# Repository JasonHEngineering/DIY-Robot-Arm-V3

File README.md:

# DIY-Robot-Arm-V3 

Introduction - https://youtu.be/GQhKxkShxAY

# Parts Cost Estimation (SGD)

| Parts | Est. Cost (SGD) | Link |
|-------|----------------:|------|
| CNC parts (including shipping cost) | 740 | [CAD file in GitHub](https://github.com/JasonHEngineering/DIY-Robot-Arm-V3/tree/main/CAD%20(2d%20%2B%20step%20files)) |
| 3d printed parts (including shipping cost) | 69 | [CAD file in GitHub](https://github.com/JasonHEngineering/DIY-Robot-Arm-V3/tree/main/CAD%20(2d%20%2B%20step%20files)) |
| Main PCBA (5x, including SMD assembly & shipping cost) | 158 | [Design files in GitHub](https://github.com/JasonHEngineering/DIY-Robot-Arm-V3/tree/main/PCBA%20(schema%2C%20gerbers%2C%20kicad%20project)) |
| Encoder PCBA (10x, including SMD assembly & shipping cost) | 132 | [Design files in GitHub](https://github.com/JasonHEngineering/DIY-Robot-Arm-V3/tree/main/PCBA%20(schema%2C%20gerbers%2C%20kicad%20project)) |
| Bearing 6805 2RS (25x37x7mm) (3x) | 16.07 | [AliExpress](https://s.click.aliexpress.com/e/_c33xzexj) |
| Bearing lock nut M24x1.5x30x5 (3x) | 6.24 | [AliExpress](https://s.click.aliexpress.com/e/_c3OO3rFf) |
| M3 set screw with nylon head | 4.84 | [AliExpress](https://s.click.aliexpress.com/e/_c3lDO1O5) |
| Pulley (Bore 8mm, belt width 6 mm, 2GT-30T) | 4.48 | [AliExpress](https://s.click.aliexpress.com/e/_c4LLe4XL) |
| Pulley (Bore 12mm, belt width 6 mm, 2GT-30T) | 3.06 | [AliExpress](https://s.click.aliexpress.com/e/_c3QfG9gt) |
| Timing belt (2GT-200-6mm) | 1.02 | [AliExpress](https://s.click.aliexpress.com/e/_c4KhaszX) |
| Diametric Magnets for encoders (10 pcs / lot) | 3.68 | [AliExpress](https://s.click.aliexpress.com/e/_c3Axm1QN) |
| FFC cables (pitch 0.5 mm) | 6.00 | [AliExpress](https://s.click.aliexpress.com/e/_c4SXa38p) |
| Stepper motor cables (XH2.54) | 10.00 | [AliExpress](https://s.click.aliexpress.com/e/_c3dAdb65) |
| Stepper motor 60mm model 17CS07A-180 (2x) | 38.64 | [AliExpress](https://s.click.aliexpress.com/e/_c2yzH5rf) |
| Stepper motor 60mm model 17HS4023 (3x) | 25.29 | [AliExpress](https://s.click.aliexpress.com/e/_c4bld957) |
| Stepper motor 60mm model 17HS3401S-SZ (1x) | 12.29 | [AliExpress](https://s.click.aliexpress.com/e/_c31tJidB) |
| X17-30A harmonic reducer (30:1) (5x) | 338.00 | [AliExpress](https://s.click.aliexpress.com/e/_c3xNHvpT) |
| Raspberry Pi 4B, 4GB | 160.00 | [AliExpress](https://s.click.aliexpress.com/e/_c45i6ECJ) |
| ESP32-S3-DevKitC-1 (n16r8) | 14.63 | [AliExpress](https://s.click.aliexpress.com/e/_c41bdQlh) |
| Pins & connectors (22 pins) | 1.91 | [AliExpress](https://s.click.aliexpress.com/e/_c3fCAogH) |
| TMC2209 V1.3 motor drivers (6x) | 24.13 | [AliExpress](https://s.click.aliexpress.com/e/_c4b6KFWH) |
| 24V fan (60x60x15mm) | 2.89 | [AliExpress](https://s.click.aliexpress.com/e/_c3T1QZcp) |
| E-Stop Button | 4.15 | [AliExpress](https://s.click.aliexpress.com/e/_c3gcdvel) |
| DOIT ESP32 DEV KIT V1 | 7.27 | [AliExpress](https://s.click.aliexpress.com/e/_c3el80wp) |
| PS controller | 13.34 | [AliExpress](https://s.click.aliexpress.com/e/_c4OqUEGd) |
| Mini-560-Pro (Mini Pro 5V, 3A for Raspberry Pi) | 1.51 | [AliExpress](https://s.click.aliexpress.com/e/_c37WkxiV) |
| Optical Experiment Plate 5052 Aluminum 280x320x8mm | 71.25 | [AliExpress](https://s.click.aliexpress.com/e/_c3tvnmLj) |
| Servo Claw | 26.26 | [AliExpress](https://s.click.aliexpress.com/e/_c3I3E3Mh) |
| Servo motor MG996R | 6.74 | [AliExpress](https://s.click.aliexpress.com/e/_c3sTutbP) |
| Standoffs, clamps, dowel pins | 10.00 | |
| Fasteners | 10.00 | |

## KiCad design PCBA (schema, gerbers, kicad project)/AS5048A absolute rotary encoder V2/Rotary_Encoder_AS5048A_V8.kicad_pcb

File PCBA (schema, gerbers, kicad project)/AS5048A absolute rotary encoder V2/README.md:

# Notes 

1) Although there are 7 jumper pads here for purpose of using these encoders in series with SPI protocol, however due to GPIO0 on ESP32-S3 being a bootstrap pin, I will not be using jumper JP5 on the absolute encoder board at all. Consequently, the remaining chip select jumper for all the 6 axis encoders are allocated as shown in the table, with the soldering done accordingly.

<!-- wp:image {"id":4006,"sizeSlug":"large","linkDestination":"none"} -->
<figure class="wp-block-image size-large"></figure>
<!-- /wp:image -->

<!-- wp:image {"id":4002,"sizeSlug":"large","linkDestination":"none"} -->
<figure class="wp-block-image size-large"></figure>
<!-- /wp:image -->

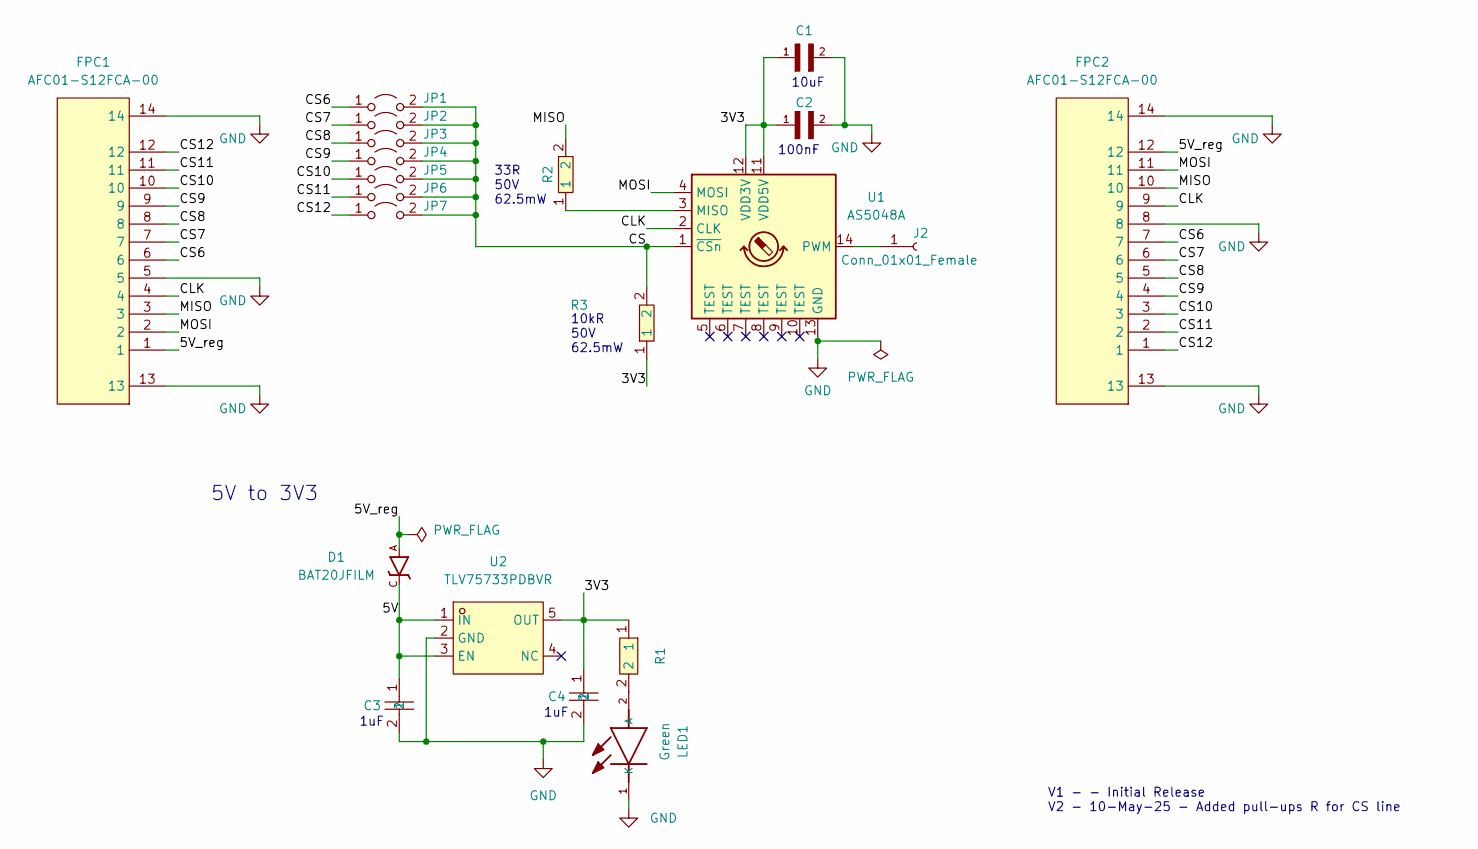
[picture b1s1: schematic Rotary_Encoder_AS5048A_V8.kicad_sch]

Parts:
C1: GRM155R60J106ME15D; CAPC1005X65N; LCSC C412251
C2: GCM155R71C104KA55J; CAPC1005X55N; LCSC C2655418
C3, C4: CC0603KRX7R7BB105; MLCC_16V_1uF_X7R_±10%_0603_C106248; LCSC Part C106248
D1: BAT20JFILM; SOD-323; LCSC Part # C155590
FPC1, FPC2: AFC01-S12FCA-00; FFC_conn_Flip type_12P_P=0.5mm_C262661; LCSC Part C262661
J2: Conn_01x01_Female; PinHeader_1x01_P1.00mm_Vertical
JP1, JP2, JP3, JP4, JP5, JP6, JP7: Jumper_2_Open; SolderJumper-2_P1.3mm_Open_TrianglePad1.0x1.5mm
LED1: Green; LEDC1608X80N; MOUSER_PART_NUMBER 710-150060GS75000
R1: 0402WGD1001TCE; Resistor_62.5mW_50V_±0.5%_1kΩ_0402_C407754; LCSC Part C407754
R2: RC0402FR-0733RL; Resistor_62.5mW_50V_±1%_33Ω_0402_C138002; LCSC Part C138002
R3: RC0402FR-0710KL; Resistor_62.5mW_50V_±1%_10kΩ_0402_C60490; LCSC Part C60490
U1: AS5048A; TSSOP-14_4.4x5mm_P0.65mm; LCSC C2655181
U2: TLV75733PDBVR; LDO_1A_Fixed_3.3V_out_5.5V_in_SOT-23-5_C485517; LCSC Part C485517

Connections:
/3V3: C1.1, C2.1, C4.1, R1.1, R3.1, U1.11 (VDD5V), U1.12 (VDD3V), U2.5 (OUT)
/5V: C3.1, D1.C, U2.1 (IN), U2.3 (EN)
/5V_reg: D1.A, FPC1.1, FPC2.12
/CLK: FPC1.4, FPC2.9, U1.2 (CLK)
/CS: JP1.2 (B), JP2.2 (B), JP3.2 (B), JP4.2 (B), JP5.2 (B), JP6.2 (B), JP7.2 (B), R3.2, U1.1 (~CSn)
/CS1: FPC1.6, FPC2.7, JP1.1 (A)
/CS2: FPC1.7, FPC2.6, JP2.1 (A)
/CS3: FPC1.8, FPC2.5, JP3.1 (A)
/CS4: FPC1.9, FPC2.4, JP4.1 (A)
/CS5: FPC1.10, FPC2.3, JP5.1 (A)
/CS6: FPC1.11, FPC2.2, JP6.1 (A)
/CS7: FPC1.12, FPC2.1, JP7.1 (A)
/MISO: FPC1.3, FPC2.10, R2.2
/MOSI: FPC1.2, FPC2.11, U1.4 (MOSI)
GND: C1.2, C2.2, C3.2, C4.2, FPC1.5, FPC1.13, FPC1.14, FPC2.8, FPC2.13, FPC2.14, LED1.1 (K), U1.13 (GND), U2.2 (GND)
unnamed: J2.1, U1.14 (PWM)
unnamed: LED1.2 (A), R1.2
unnamed: R2.1, U1.3 (MISO)

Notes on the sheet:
100nF
10kR 50V 62.5mW
1uF
33R 50V 62.5mW
5V to 3V3
10uF
V1 - - Initial Release V2 - 10-May-25 - Added pull-ups R for CS line

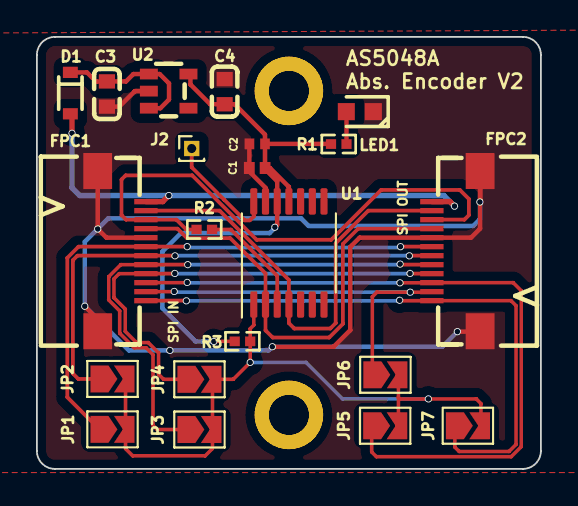
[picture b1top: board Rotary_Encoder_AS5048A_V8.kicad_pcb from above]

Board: 2 copper layers, 28.0 x 24.0 mm, 21 parts (0 on the bottom side), 18 nets.

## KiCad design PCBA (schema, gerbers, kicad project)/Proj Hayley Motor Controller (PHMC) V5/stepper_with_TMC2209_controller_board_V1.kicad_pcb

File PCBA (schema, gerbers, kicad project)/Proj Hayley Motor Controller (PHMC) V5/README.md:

# Notes 

1) Proven working in Arduino IDE 2.3.7
2) Servo is indeed GPIO 38 (J6 - pin 3), instead of the initial intent of GPIO 43 (J13 - pin 3), because the serial com line is always busy
3) JTAG must be disabled - because all the pins are used for the purpose of motor driving or some functions already

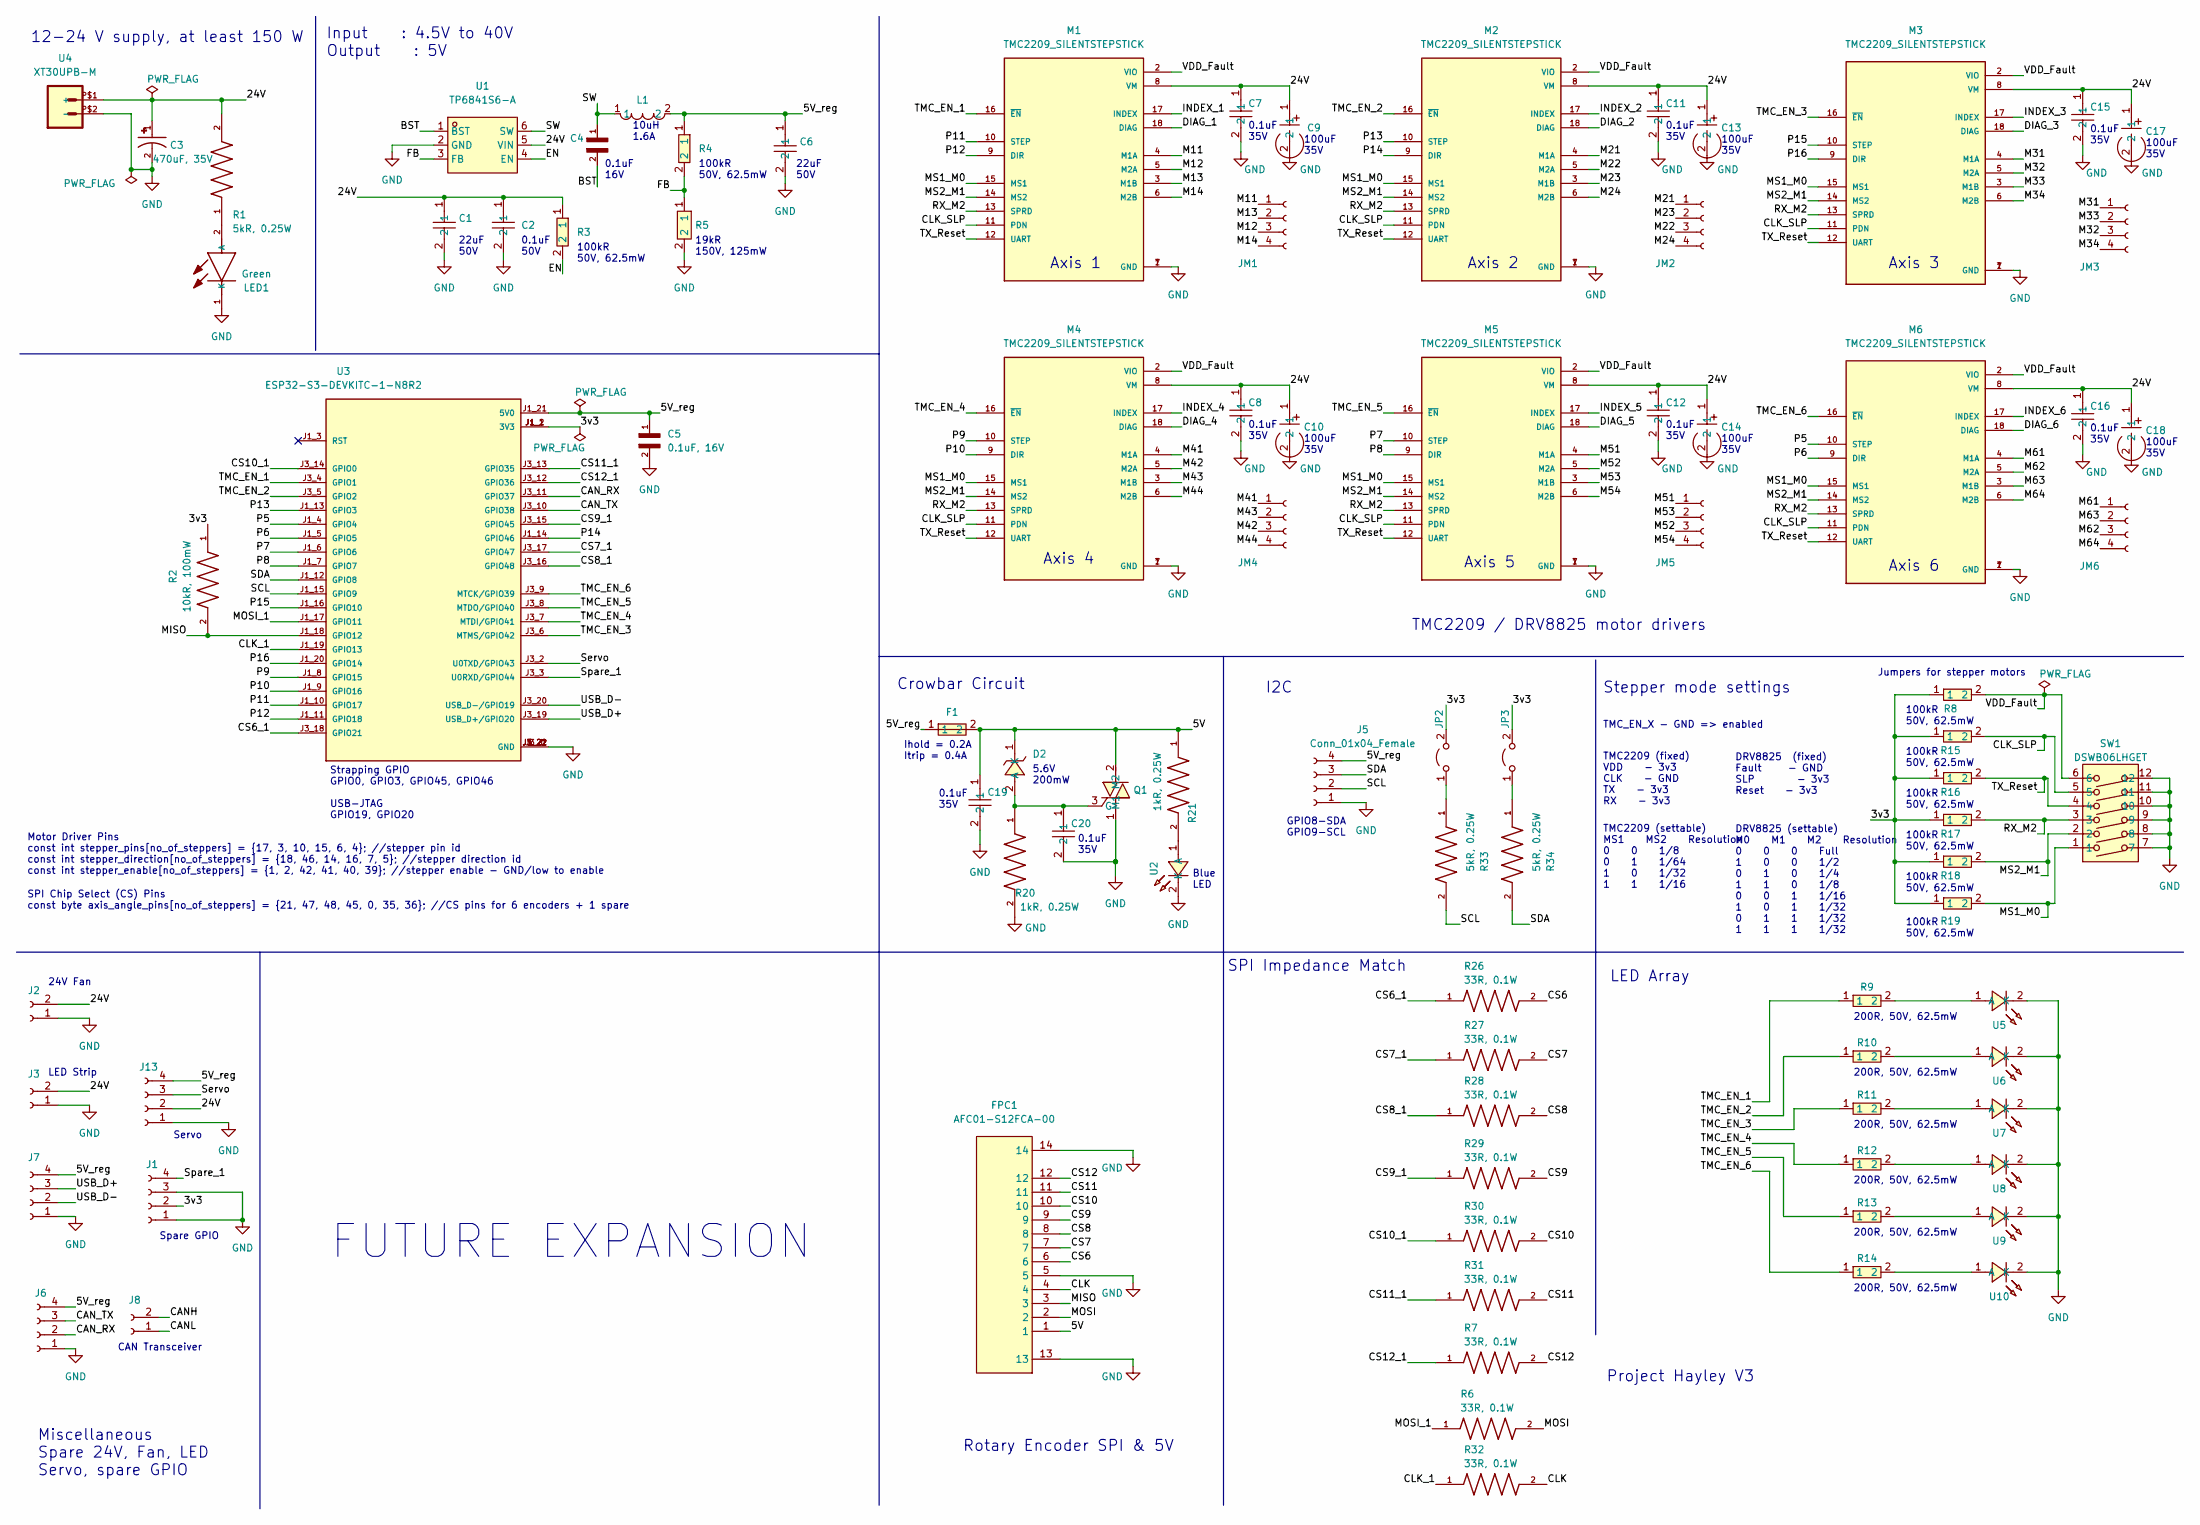
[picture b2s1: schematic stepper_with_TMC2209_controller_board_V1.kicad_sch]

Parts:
C1, C6: FS55X226K500EHG; Cap_MLCC_50V_22uF_X7R_2220_C784103; LCSC Part C784103
C2: CC0603KRX7R9BB104; MLCC_Yageo_50V_100nF_X7R_±10%_0603_C14663; LCSC Part C14663
C3: 470uF, 35V; CAP_EEHZS1V471P; PARTREV 30-Sep-20; LCSC C403803
C4: GCM155R71C104KA55J; CAPC1005X55N; LCSC Part # C2655418
C5: 0.1uF, 16V; CAPC1005X55N; LCSC C71629
C7, C8, C11, C12, C15, C16, C19, C20: CGA2B3X7R1V104KT0Y0F; C0402_L1.0-W0.5-H0.5; LCSC Part C343047
C9, C10, C13, C14, C17, C18: RVT1V101M0605; Capacitor_100uF_35V_75mA@120Hz_±20%_D6pt3xL5pt4mm_C3151830; LCSC Part C3151830
D2: BZT52C5V6S_C19077441; SOD-323_L1.7-W1.3-LS2.6-RD; LCSC Part C19077441
F1: 0ZCJ0020FF2E; F1206; LCSC Part C6964258
FPC1: AFC01-S12FCA-00; FFC_conn_Flip type_12P_P=0.5mm_C262661; LCSC Part C262661
J1, J5, J7, J13: Conn_01x04_Female; JST_PH_B4B-PH-K_1x04_P2.00mm_Vertical
J2, J3, J8: Conn_01x02_Female; JST_EH_B2B-EH-A_1x02_P2.50mm_Vertical
J6: Conn_01x04_Female; JST_EH_B4B-EH-A_1x04_P2.50mm_Vertical
JM1, JM2, JM3, JM4, JM5, JM6: Conn_01x04_Female; JST_XH_B4B-XH-A_1x04_P2.50mm_Vertical
JP2, JP3: Jumper_2_Open; SolderJumper-2_P1.3mm_Open_TrianglePad1.0x1.5mm
L1: FTC252012S100MBCA; Inductor_10uH_1pt6A_2x2pt5mm_C5832376; LCSC Part C5832376
LED1: Green; LEDC1608X80N; MOUSER_PART_NUMBER 710-150060GS75000
M1, M2, M3, M4, M5, M6: TMC2209_SILENTSTEPSTICK; MODULE_TMC2209_SILENTSTEPSTICK; PARTREV 1.20
Q1: MAC97A8-23-3L; SOT-23-3_L2.9-W1.6-P1.90-LS2.8-BL-A; LCSC Part C2831929
R1, R33, R34: 5kR, 0.25W; RESC3116X65N; LCSC Part # C870818
R2: 10kR, 100mW; RESC1607X60N; LCSC Part # C98220
R3, R4, R8, R15, R16, R17, R18, R19: RC0402FR-07100KL; Resistor_ 100kΩ_62.5mW_50V_0402_C60491; LCSC Part C60491
R5: FRC0805F1902TS; Resistor_19kΩ_0.125W_150V_0805_C2930177; LCSC Part C2930177
R6, R7, R26, R27, R28, R29, R30, R31, R32: 33R, 0.1W; RESC1608X55N; LCSC Part # C108407
R9, R10, R11, R12, R13, R14: 0402WGF2000TCE; R0402; LCSC Part C25087
R20, R21: 1kR, 0.25W; RESC3116X65N; LCSC Part # C131398
SW1: DSWB06LHGET; 6_SPST_Through_Hole_DIP_C99416; LCSC Part C99416
U1: TP6841S6-A; SOT-23-6_L2.9-W1.6-P0.95-LS2.8-BL; LCSC Part C2844924
U2, U5, U6, U7, U8, U9, U10: XL-1608UBC-06A; Blue_LED_5mA_456nm~476nm_130°_2.6V~3V_0603_C7371904; LCSC Part C7371904
U3: ESP32-S3-DEVKITC-1-N8R2; XCVR_ESP32-S3-DEVKITC-1-N8R2; PARTREV V1
U4: XT30UPB-M; LCSC Part # C108769

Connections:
/3v3: J1.2, JP2.2 (B), JP3.2 (B), R2.1, R8.1, R15.1, R16.1, R17.1, R18.1, R19.1, U3.J1_1 (3V3), U3.J1_2 (3V3)
/5V: C19.1, D2.1 (K), F1.2, FPC1.1, Q1.2 (M2), R21.1
/5V_reg: C5.1, C6.1, F1.1, J5.4, J6.4, J7.4, J13.4, L1.2, R4.1, U3.J1_21 (5V0)
/24V: C1.1, C2.1, C3.1, C7.1, C8.1, C9.1, C10.1, C11.1, C12.1, C13.1, C14.1, C15.1, C16.1, C17.1, C18.1, J2.2, J3.2, J13.2, M1.8 (VM), M2.8 (VM), M3.8 (VM), M4.8 (VM), M5.8 (VM), M6.8 (VM), R1.2, R3.1, U1.5 (VIN), U4.P$1 (+)
/BST: C4.2, U1.1 (BST)
/CANH: J8.2
/CANL: J8.1
/CAN_RX: J6.2, U3.J3_11 (GPIO37)
/CAN_TX: J6.3, U3.J3_10 (GPIO38)
/CLK: FPC1.4, R32.2
/CLK_1: R32.1, U3.J1_19 (GPIO13)
/CLK_SLP: M1.11 (PDN), M2.11 (PDN), M3.11 (PDN), M4.11 (PDN), M5.11 (PDN), M6.11 (PDN), R15.2, SW1.5
/CS6: FPC1.6, R26.2
/CS6_1: R26.1, U3.J3_18 (GPIO21)
/CS7: FPC1.7, R27.2
/CS7_1: R27.1, U3.J3_17 (GPIO47)
/CS8: FPC1.8, R28.2
/CS8_1: R28.1, U3.J3_16 (GPIO48)
/CS9: FPC1.9, R29.2
/CS9_1: R29.1, U3.J3_15 (GPIO45)
/CS10: FPC1.10, R30.2
/CS10_1: R30.1, U3.J3_14 (GPIO0)
/CS11: FPC1.11, R31.2
/CS11_1: R31.1, U3.J3_13 (GPIO35)
/CS12: FPC1.12, R7.2
/CS12_1: R7.1, U3.J3_12 (GPIO36)
/DIAG_1: M1.18 (DIAG)
/DIAG_2: M2.18 (DIAG)
/DIAG_3: M3.18 (DIAG)
/DIAG_4: M4.18 (DIAG)
/DIAG_5: M5.18 (DIAG)
/DIAG_6: M6.18 (DIAG)
/EN: R3.2, U1.4 (EN)
/FB: R4.2, R5.1, U1.3 (FB)
/INDEX_1: M1.17 (INDEX)
/INDEX_2: M2.17 (INDEX)
/INDEX_3: M3.17 (INDEX)
/INDEX_4: M4.17 (INDEX)
/INDEX_5: M5.17 (INDEX)
/INDEX_6: M6.17 (INDEX)
/M11: JM1.1, M1.4 (M1A)
/M12: JM1.3, M1.5 (M2A)
/M13: JM1.2, M1.3 (M1B)
/M14: JM1.4, M1.6 (M2B)
/M21: JM2.1, M2.4 (M1A)
/M22: JM2.3, M2.5 (M2A)
/M23: JM2.2, M2.3 (M1B)
/M24: JM2.4, M2.6 (M2B)
/M31: JM3.1, M3.4 (M1A)
/M32: JM3.3, M3.5 (M2A)
/M33: JM3.2, M3.3 (M1B)
/M34: JM3.4, M3.6 (M2B)
/M41: JM4.1, M4.4 (M1A)
/M42: JM4.3, M4.5 (M2A)
/M43: JM4.2, M4.3 (M1B)
/M44: JM4.4, M4.6 (M2B)
/M51: JM5.1, M5.4 (M1A)
/M52: JM5.3, M5.5 (M2A)
/M53: JM5.2, M5.3 (M1B)
/M54: JM5.4, M5.6 (M2B)
/M61: JM6.1, M6.4 (M1A)
/M62: JM6.3, M6.5 (M2A)
/M63: JM6.2, M6.3 (M1B)
/M64: JM6.4, M6.6 (M2B)
/MISO: FPC1.3, R2.2, U3.J1_18 (GPIO12)
/MOSI: FPC1.2, R6.2
/MOSI_1: R6.1, U3.J1_17 (GPIO11)
/MS1_M0: M1.15 (MS1), M2.15 (MS1), M3.15 (MS1), M4.15 (MS1), M5.15 (MS1), M6.15 (MS1), R19.2, SW1.1
/MS2_M1: M1.14 (MS2), M2.14 (MS2), M3.14 (MS2), M4.14 (MS2), M5.14 (MS2), M6.14 (MS2), R18.2, SW1.2
/P5: M6.10 (STEP), U3.J1_4 (GPIO4)
/P6: M6.9 (DIR), U3.J1_5 (GPIO5)
/P7: M5.10 (STEP), U3.J1_6 (GPIO6)
/P8: M5.9 (DIR), U3.J1_7 (GPIO7)
/P9: M4.10 (STEP), U3.J1_8 (GPIO15)
/P10: M4.9 (DIR), U3.J1_9 (GPIO16)
/P11: M1.10 (STEP), U3.J1_10 (GPIO17)
/P12: M1.9 (DIR), U3.J1_11 (GPIO18)
/P13: M2.10 (STEP), U3.J1_13 (GPIO3)
/P14: M2.9 (DIR), U3.J1_14 (GPIO46)
/P15: M3.10 (STEP), U3.J1_16 (GPIO10)
/P16: M3.9 (DIR), U3.J1_20 (GPIO14)
/RX_M2: M1.13 (SPRD), M2.13 (SPRD), M3.13 (SPRD), M4.13 (SPRD), M5.13 (SPRD), M6.13 (SPRD), R17.2, SW1.3
/SCL: J5.2, R33.2, U3.J1_15 (GPIO9)
/SDA: J5.3, R34.2, U3.J1_12 (GPIO8)
/SW: C4.1, L1.1, U1.6 (SW)
/Servo: J13.3, U3.J3_2 (U0TXD/GPIO43)
/Spare_1: J1.4, U3.J3_3 (U0RXD/GPIO44)
/TMC_EN_1: M1.16 (~EN), R9.1, U3.J3_4 (GPIO1)
/TMC_EN_2: M2.16 (~EN), R10.1, U3.J3_5 (GPIO2)
/TMC_EN_3: M3.16 (~EN), R11.1, U3.J3_6 (MTMS/GPIO42)
/TMC_EN_4: M4.16 (~EN), R12.1, U3.J3_7 (MTDI/GPIO41)
/TMC_EN_5: M5.16 (~EN), R13.1, U3.J3_8 (MTDO/GPIO40)
/TMC_EN_6: M6.16 (~EN), R14.1, U3.J3_9 (MTCK/GPIO39)
/TX_Reset: M1.12 (UART), M2.12 (UART), M3.12 (UART), M4.12 (UART), M5.12 (UART), M6.12 (UART), R16.2, SW1.4
/USB_D+: J7.3, U3.J3_19 (USB_D+/GPIO20)
/USB_D-: J7.2, U3.J3_20 (USB_D-/GPIO19)
/VDD_Fault: M1.2 (VIO), M2.2 (VIO), M3.2 (VIO), M4.2 (VIO), M5.2 (VIO), M6.2 (VIO), R8.2, SW1.6
GND: C1.2, C2.2, C3.2, C5.2, C6.2, C7.2, C8.2, C9.2, C10.2, C11.2, C12.2, C13.2, C14.2, C15.2, C16.2, C17.2, C18.2, C19.2, C20.2, FPC1.5, FPC1.13, FPC1.14, J1.1, J1.3, J2.1, J3.1, J5.1, J6.1, J7.1, J13.1, LED1.1 (K), M1.1 (GND), M1.7 (GND), M2.1 (GND), M2.7 (GND), M3.1 (GND), M3.7 (GND), M4.1 (GND), M4.7 (GND), M5.1 (GND), M5.7 (GND), M6.1 (GND), M6.7 (GND), Q1.1 (M1), R5.2, R20.2, SW1.7, SW1.8, SW1.9, SW1.10, SW1.11, SW1.12, U1.2 (GND), U2.2 (K), U3.J1_22 (GND), U3.J3_1 (GND), U3.J3_21 (GND), U3.J3_22 (GND), U4.P$2 (-), U5.2 (K), U6.2 (K), U7.2 (K), U8.2 (K), U9.2 (K), U10.2 (K)
unnamed: C20.1, D2.2 (A), Q1.3 (G), R20.1
unnamed: JP2.1 (A), R33.1
unnamed: JP3.1 (A), R34.1
unnamed: LED1.2 (A), R1.1
unnamed: R9.2, U5.1 (A)
unnamed: R10.2, U6.1 (A)
unnamed: R11.2, U7.1 (A)
unnamed: R12.2, U8.1 (A)
unnamed: R13.2, U9.1 (A)
unnamed: R14.2, U10.1 (A)
unnamed: R21.2, U2.1 (A)

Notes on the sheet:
100uF 35V
Jumpers for stepper motors
TMC2209 (fixed) VDD - 3v3 CLK - GND TX - 3v3 RX - 3v3
Project Hayley V3
100kR 50V, 62.5mW
Miscellaneous Spare 24V, Fan, LED Servo, spare GPIO
0.1uF 35V
200R, 50V, 62.5mW
22uF 50V
DRV8825 (settable) M0 M1 M2 Resolution 0 0 0 Full 1 0 0 1/2 0 1 0 1/4 1 1 0 1/8 0 0 1 1/16 1 0 1 1/32 0 1 1 1/32 1 1 1 1/32
Crowbar Circuit
Spare GPIO
Axis 2
Rotary Encoder SPI & 5V
0.1uF 50V
10uH 1.6A
0.1uF 16V
Axis 1
GPIO8-SDA GPIO9-SCL
19kR 150V, 125mW
TMC2209 (settable) MS1 MS2 Resolution 0 0 1/8 0 1 1/64 1 0 1/32 1 1 1/16
Strapping GPIO GPIO0, GPIO3, GPIO45, GPIO46 USB-JTAG GPIO19, GPIO20
LED Array
SPI Chip Select (CS) Pins const byte axis_angle_pins[no_of_steppers] = {21, 47, 48, 45, 0, 35, 36}; //CS pins for 6 encoders + 1 spare
Servo
DRV8825 (fixed) Fault - GND SLP - 3v3 Reset - 3v3
Stepper mode settings
TMC_EN_X - GND => enabled
Axis 6
5.6V 200mW
LED Strip
SPI Impedance Match
I2C
Input : 4.5V to 40V Output : 5V
Axis 3
24V Fan
Ihold = 0.2A Itrip = 0.4A
Axis 4
Blue LED
FUTURE EXPANSION

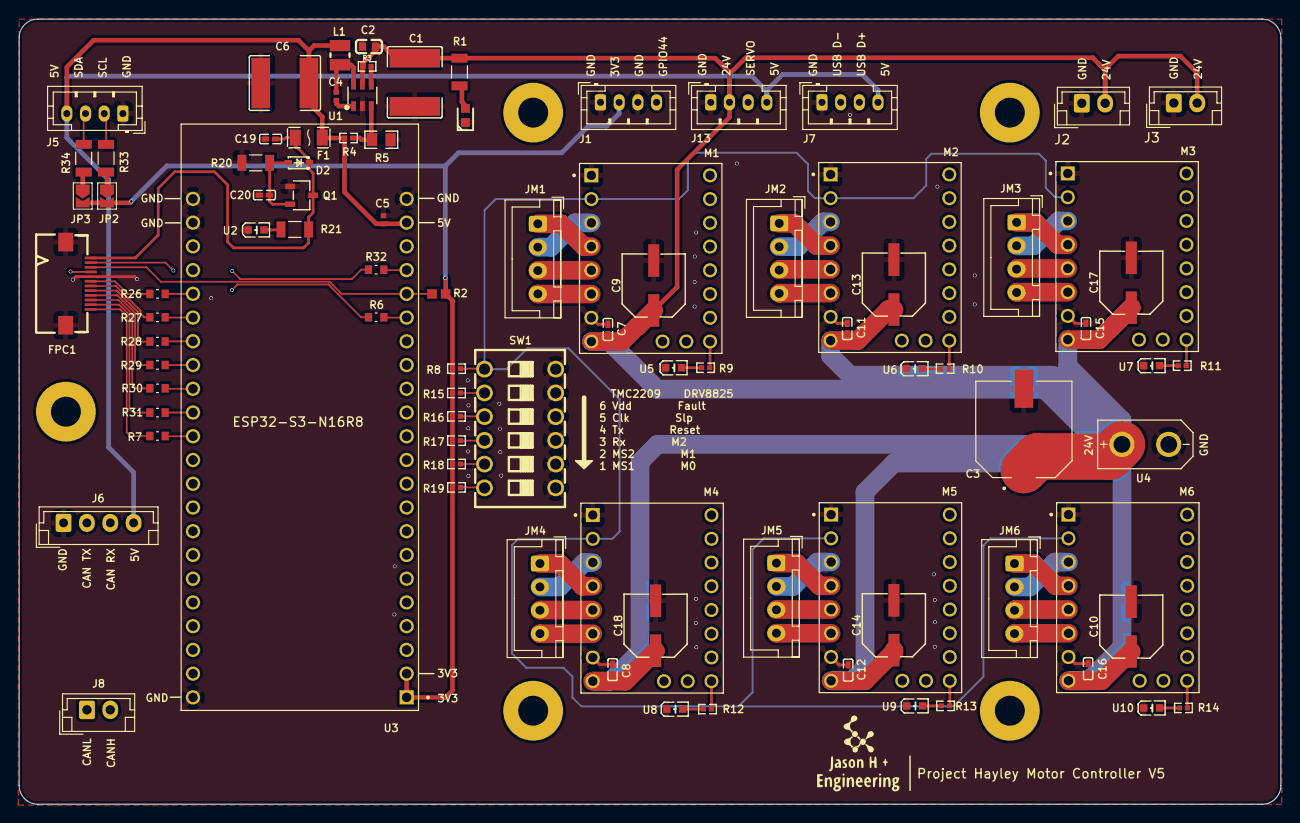
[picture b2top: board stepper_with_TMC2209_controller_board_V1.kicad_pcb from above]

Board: 4 copper layers, 135.0 x 84.0 mm, 89 parts (0 on the bottom side), 95 nets.

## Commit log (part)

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2025-09-02 Initial Upload
    Initial upload for sub-system test: 1 stepper + 1 encoder
2025-10-05 Uploading PCBA project files
    KiCAD files - both absolute encoder as well as the motor controller adaptor board
2025-10-13 CAD upload
    Step files and drawings done in OnShape
2025-12-16 Raspberry Pi hosted GUI
    Python based - plotly dash.
2025-12-16 Create Project_Hayley_ESP32_V12.ino
    Initial upload - compatible with Project_Hayley_V5_IK_user_interface_V01.py
2025-12-24 Update to enable/disable stepper motor
2025-12-31 Significant updates to both codes on raspberry Pi and ESP32
    ESP32 update to operate in dual core mode and also the ability to disable the stepper motor drivers, so as to manipulate the positions of arms. Also added CSV recording ability (learning capability)
    Project_Hayley_V5_IK_user_interface_V04.py
    V04 add capability to record robot arm positions (disable motor), save to csv for repeat later
    Compaitible with "Project_Hayley_ESP32_V14.ino"
    Project_Hayley_ESP32_V14.ino
    V14 - major revamp to go dual core mode
2026-01-04 Create Project_Hayley_ESP32_V15.ino
    Project_Hayley_ESP32_V15 - added "QueueHandle_t jointQueue;" in order to manage stack of back-to-back angle move request from raspberry pi. Can handle 100 queue at once.
2026-01-12 Create Project_Hayley_ESP32_V16.ino
    V16 - create standalone Kp, Ki, Kd constants for each axis
    - Introduce slight speed balancing between the axis motion, pegged to the axis with the longer travel time
    - Compatible with "Project_Hayley_V5_IK_user_interface_V04.py"
2026-01-21 servo basic check
    subsystem: servo sanity check
2026-01-23 Added servo function
    Servo function added in "Project_Hayley_V5_IK_user_interface_V05.py" and "Project_Hayley_ESP32_V17.ino"
2026-02-02 General update
    General updates as indicated in history - but more important one is regarding the accounting of magnet encoder direction.
2026-04-16 Update V18 and add V19
    V18 - fixed USB serial bug
    V19 - placeholder, will be updated again
2026-04-19 Update Project_Hayley_ESP32_V19.ino
    Temporary update - before cleanup
2026-04-26 Create Project_Hayley_ESP32_V20.ino
    Interim update for V20
    V20 - Added ESP-NOW communication protocol for use with PS controller
    - Added safety angle limits motor cut-off
    - Compatible with "Project_Hayley_V5_IK_user_interface_V07.py"
2026-05-03 Checkpoint update
    Update, before cleanup.
    ESP32-DevKitC-1 (N16R8) -
    Project_Hayley_ESP32_V20.ino
    Raspberry Pi 3B and above -
    Project_Hayley_V5_IK_user_interface_V08.py
    DOIT ESP32 DEVKIT V1 -
2026-06-14 Update for PS controller bug
